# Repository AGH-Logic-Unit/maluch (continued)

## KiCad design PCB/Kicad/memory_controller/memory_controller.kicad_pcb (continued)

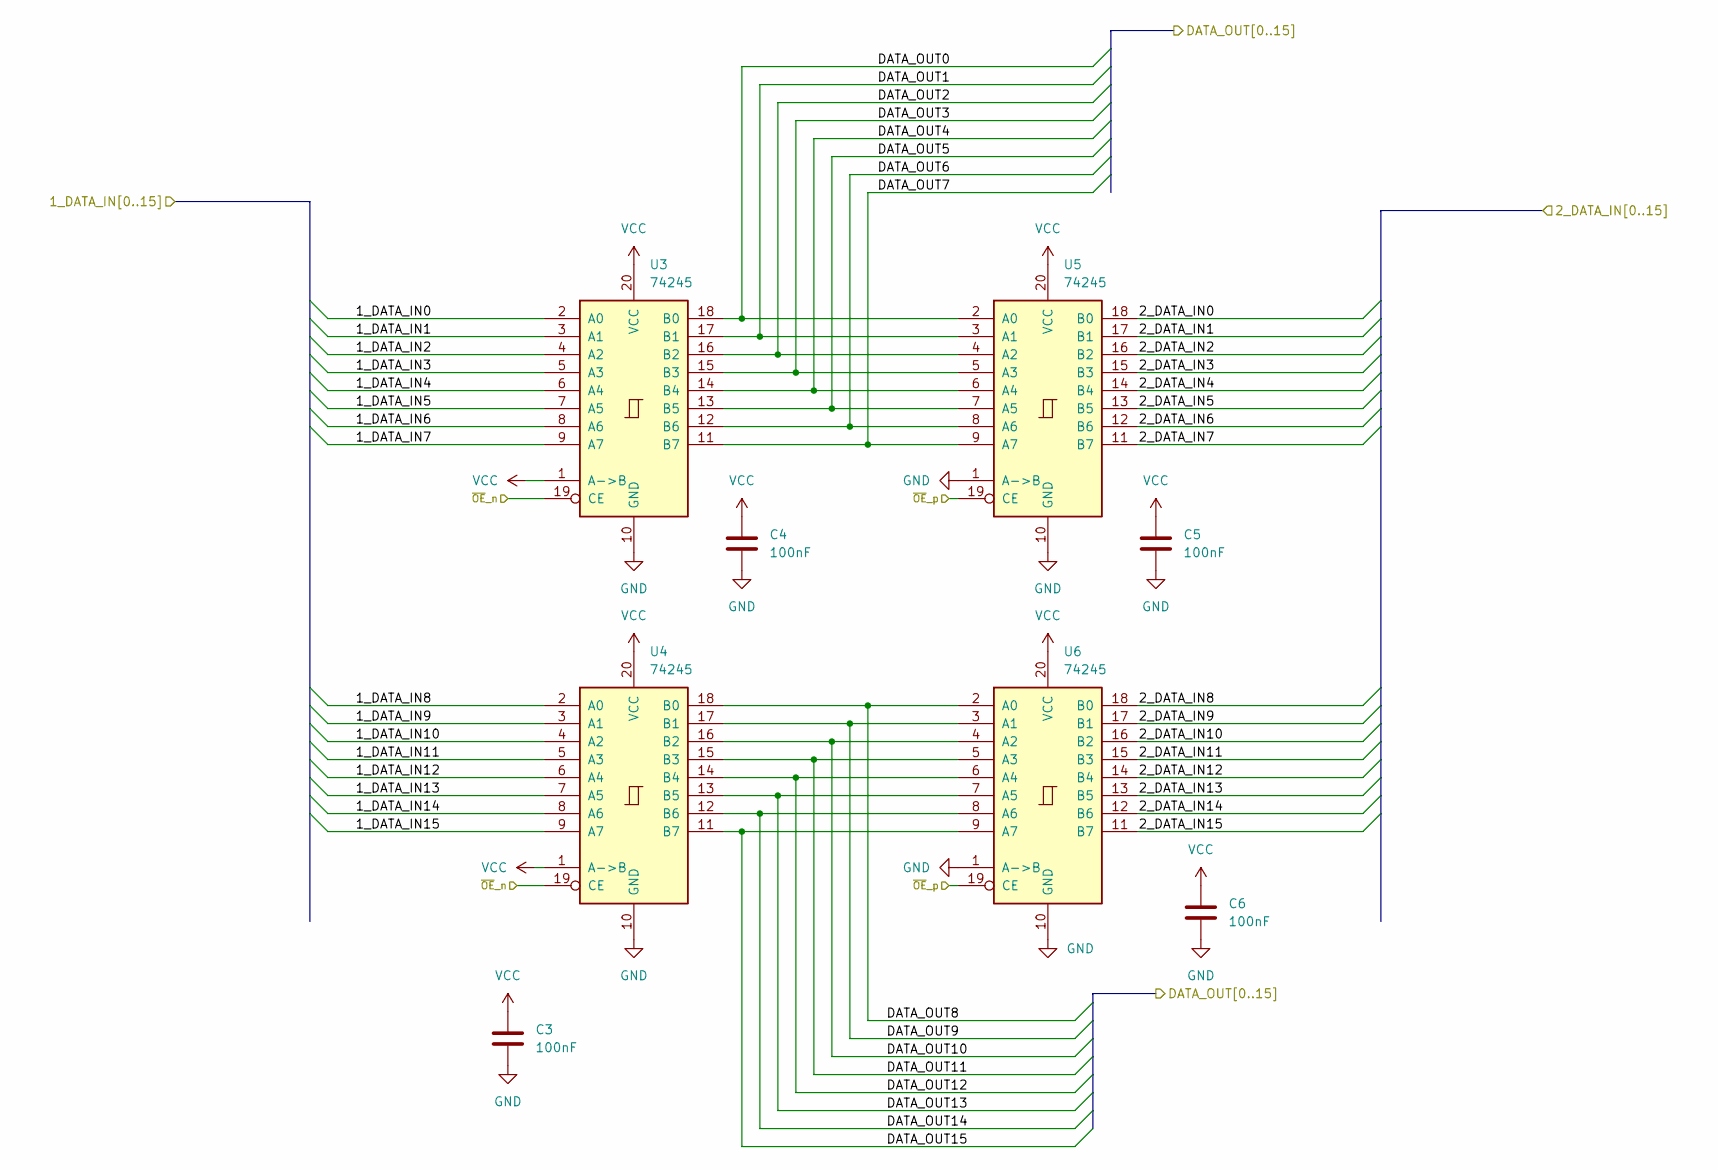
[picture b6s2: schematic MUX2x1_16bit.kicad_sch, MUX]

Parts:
C3, C4, C5, C6: 100nF; C_0402_1005Metric
U3, U4, U5, U6: 74245; TSSOP-20_4.4x6.5mm_P0.65mm

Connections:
/ADDER/DATA_OUT0: U5.18 (B0); also elsewhere on the board
/ADDER/DATA_OUT1: U5.17 (B1); also elsewhere on the board
/ADDER/DATA_OUT2: U5.16 (B2); also elsewhere on the board
/ADDER/DATA_OUT3: U5.15 (B3); also elsewhere on the board
/ADDER/DATA_OUT4: U5.14 (B4); also elsewhere on the board
/ADDER/DATA_OUT5: U5.13 (B5); also elsewhere on the board
/ADDER/DATA_OUT6: U5.12 (B6); also elsewhere on the board
/ADDER/DATA_OUT7: U5.11 (B7); also elsewhere on the board
/ADDER/DATA_OUT8: U6.18 (B0); also elsewhere on the board
/ADDER/DATA_OUT9: U6.17 (B1); also elsewhere on the board
/ADDER/DATA_OUT10: U6.16 (B2); also elsewhere on the board
/ADDER/DATA_OUT11: U6.15 (B3); also elsewhere on the board
/ADDER/DATA_OUT12: U6.14 (B4); also elsewhere on the board
/ADDER/DATA_OUT13: U6.13 (B5); also elsewhere on the board
/ADDER/DATA_OUT14: U6.12 (B6); also elsewhere on the board
/ADDER/DATA_OUT15: U6.11 (B7); also elsewhere on the board
/GPU_DATA0: U3.2 (A0); also elsewhere on the board
/GPU_DATA1: U3.3 (A1); also elsewhere on the board
/GPU_DATA2: U3.4 (A2); also elsewhere on the board
/GPU_DATA3: U3.5 (A3); also elsewhere on the board
/GPU_DATA4: U3.6 (A4); also elsewhere on the board
/GPU_DATA5: U3.7 (A5); also elsewhere on the board
/GPU_DATA6: U3.8 (A6); also elsewhere on the board
/GPU_DATA7: U3.9 (A7); also elsewhere on the board
/GPU_DATA8: U4.2 (A0); also elsewhere on the board
/GPU_DATA9: U4.3 (A1); also elsewhere on the board
/GPU_DATA10: U4.4 (A2); also elsewhere on the board
/GPU_DATA11: U4.5 (A3); also elsewhere on the board
/GPU_DATA12: U4.6 (A4); also elsewhere on the board
/GPU_DATA13: U4.7 (A5); also elsewhere on the board
/GPU_DATA14: U4.8 (A6); also elsewhere on the board
/GPU_DATA15: U4.9 (A7); also elsewhere on the board
/RegAddr/DATA_IN0: U3.18 (B0), U5.2 (A0); also elsewhere on the board
/RegAddr/DATA_IN1: U3.17 (B1), U5.3 (A1); also elsewhere on the board
/RegAddr/DATA_IN2: U3.16 (B2), U5.4 (A2); also elsewhere on the board
/RegAddr/DATA_IN3: U3.15 (B3), U5.5 (A3); also elsewhere on the board
/RegAddr/DATA_IN4: U3.14 (B4), U5.6 (A4); also elsewhere on the board
/RegAddr/DATA_IN5: U3.13 (B5), U5.7 (A5); also elsewhere on the board
/RegAddr/DATA_IN6: U3.12 (B6), U5.8 (A6); also elsewhere on the board
/RegAddr/DATA_IN7: U3.11 (B7), U5.9 (A7); also elsewhere on the board
/RegAddr/DATA_IN8: U4.18 (B0), U6.2 (A0); also elsewhere on the board
/RegAddr/DATA_IN9: U4.17 (B1), U6.3 (A1); also elsewhere on the board
/RegAddr/DATA_IN10: U4.16 (B2), U6.4 (A2); also elsewhere on the board
/RegAddr/DATA_IN11: U4.15 (B3), U6.5 (A3); also elsewhere on the board
/RegAddr/DATA_IN12: U4.14 (B4), U6.6 (A4); also elsewhere on the board
/RegAddr/DATA_IN13: U4.13 (B5), U6.7 (A5); also elsewhere on the board
/RegAddr/DATA_IN14: U4.12 (B6), U6.8 (A6); also elsewhere on the board
/RegAddr/DATA_IN15: U4.11 (B7), U6.9 (A7); also elsewhere on the board
/~OE_n: U3.19 (CE), U4.19 (CE); also elsewhere on the board
/~OE_p: U5.19 (CE), U6.19 (CE); also elsewhere on the board
GND: C3.1, C4.1, C5.1, C6.1, U3.10 (GND), U4.10 (GND), U5.1 (A->B), U5.10 (GND), U6.1 (A->B), U6.10 (GND); also elsewhere on the board
VCC: C3.2, C4.2, C5.2, C6.2, U3.1 (A->B), U3.20 (VCC), U4.1 (A->B), U4.20 (VCC), U5.20 (VCC), U6.20 (VCC); also elsewhere on the board

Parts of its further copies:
C15, C16, C17, C18: 100nF; C_0402_1005Metric
U15, U16, U17, U18: 74245; TSSOP-20_4.4x6.5mm_P0.65mm

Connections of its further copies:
/2xROM_AT28C256/IO0: U15.2 (A0); also elsewhere on the board
/2xROM_AT28C256/IO1: U15.3 (A1); also elsewhere on the board
/2xROM_AT28C256/IO2: U15.4 (A2); also elsewhere on the board
/2xROM_AT28C256/IO3: U15.5 (A3); also elsewhere on the board
/2xROM_AT28C256/IO4: U15.6 (A4); also elsewhere on the board
/2xROM_AT28C256/IO5: U15.7 (A5); also elsewhere on the board
/2xROM_AT28C256/IO6: U15.8 (A6); also elsewhere on the board
/2xROM_AT28C256/IO7: U15.9 (A7); also elsewhere on the board
/2xROM_AT28C256/IO8: U16.2 (A0); also elsewhere on the board
/2xROM_AT28C256/IO9: U16.3 (A1); also elsewhere on the board
/2xROM_AT28C256/IO10: U16.4 (A2); also elsewhere on the board
/2xROM_AT28C256/IO11: U16.5 (A3); also elsewhere on the board
/2xROM_AT28C256/IO12: U16.6 (A4); also elsewhere on the board
/2xROM_AT28C256/IO13: U16.7 (A5); also elsewhere on the board
/2xROM_AT28C256/IO14: U16.8 (A6); also elsewhere on the board
/2xROM_AT28C256/IO15: U16.9 (A7); also elsewhere on the board
/GPU_ADDR15: U15.19 (CE), U16.19 (CE); also elsewhere on the board
/GPU_DATA0: U17.18 (B0); also elsewhere on the board
/GPU_DATA1: U17.17 (B1); also elsewhere on the board
/GPU_DATA2: U17.16 (B2); also elsewhere on the board
/GPU_DATA3: U17.15 (B3); also elsewhere on the board
/GPU_DATA4: U17.14 (B4); also elsewhere on the board
/GPU_DATA5: U17.13 (B5); also elsewhere on the board
/GPU_DATA6: U17.12 (B6); also elsewhere on the board
/GPU_DATA7: U17.11 (B7); also elsewhere on the board
/GPU_DATA8: U18.18 (B0); also elsewhere on the board
/GPU_DATA9: U18.17 (B1); also elsewhere on the board
/GPU_DATA10: U18.16 (B2); also elsewhere on the board
/GPU_DATA11: U18.15 (B3); also elsewhere on the board
/GPU_DATA12: U18.14 (B4); also elsewhere on the board
/GPU_DATA13: U18.13 (B5); also elsewhere on the board
/GPU_DATA14: U18.12 (B6); also elsewhere on the board
/GPU_DATA15: U18.11 (B7); also elsewhere on the board
/output_MUX/DATA_OUT0: U15.18 (B0), U17.2 (A0); also elsewhere on the board
/output_MUX/DATA_OUT1: U15.17 (B1), U17.3 (A1); also elsewhere on the board
/output_MUX/DATA_OUT2: U15.16 (B2), U17.4 (A2); also elsewhere on the board
/output_MUX/DATA_OUT3: U15.15 (B3), U17.5 (A3); also elsewhere on the board
/output_MUX/DATA_OUT4: U15.14 (B4), U17.6 (A4); also elsewhere on the board
/output_MUX/DATA_OUT5: U15.13 (B5), U17.7 (A5); also elsewhere on the board
/output_MUX/DATA_OUT6: U15.12 (B6), U17.8 (A6); also elsewhere on the board
/output_MUX/DATA_OUT7: U15.11 (B7), U17.9 (A7); also elsewhere on the board
/output_MUX/DATA_OUT8: U16.18 (B0), U18.2 (A0); also elsewhere on the board
/output_MUX/DATA_OUT9: U16.17 (B1), U18.3 (A1); also elsewhere on the board
/output_MUX/DATA_OUT10: U16.16 (B2), U18.4 (A2); also elsewhere on the board
/output_MUX/DATA_OUT11: U16.15 (B3), U18.5 (A3); also elsewhere on the board
/output_MUX/DATA_OUT12: U16.14 (B4), U18.6 (A4); also elsewhere on the board
/output_MUX/DATA_OUT13: U16.13 (B5), U18.7 (A5); also elsewhere on the board
/output_MUX/DATA_OUT14: U16.12 (B6), U18.8 (A6); also elsewhere on the board
/output_MUX/DATA_OUT15: U16.11 (B7), U18.9 (A7); also elsewhere on the board
/~OE_MUX_n: U17.19 (CE), U18.19 (CE); also elsewhere on the board
GND: C15.1, C16.1, C17.1, C18.1, U15.10 (GND), U16.10 (GND), U17.1 (A->B), U17.10 (GND), U18.1 (A->B), U18.10 (GND); also elsewhere on the board
VCC: C15.2, C16.2, C17.2, C18.2, U15.1 (A->B), U15.20 (VCC), U16.1 (A->B), U16.20 (VCC), U17.20 (VCC), U18.20 (VCC); also elsewhere on the board

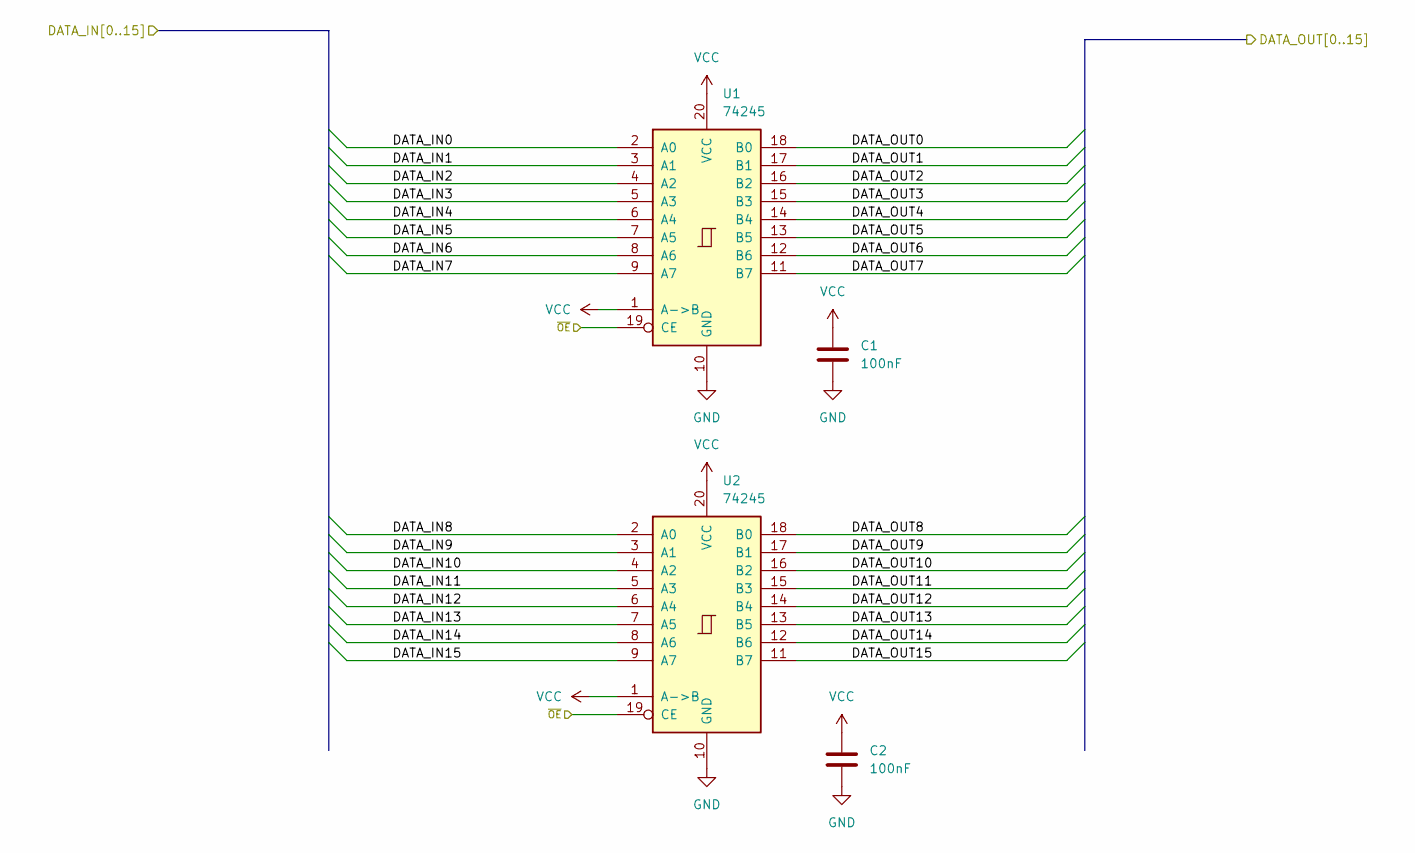
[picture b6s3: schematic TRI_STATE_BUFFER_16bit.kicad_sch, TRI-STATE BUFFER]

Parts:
C1, C2: 100nF; C_0402_1005Metric
U1, U2: 74245; TSSOP-20_4.4x6.5mm_P0.65mm

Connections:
/DATA_BUS0: U1.2 (A0); also elsewhere on the board
/DATA_BUS1: U1.3 (A1); also elsewhere on the board
/DATA_BUS2: U1.4 (A2); also elsewhere on the board
/DATA_BUS3: U1.5 (A3); also elsewhere on the board
/DATA_BUS4: U1.6 (A4); also elsewhere on the board
/DATA_BUS5: U1.7 (A5); also elsewhere on the board
/DATA_BUS6: U1.8 (A6); also elsewhere on the board
/DATA_BUS7: U1.9 (A7); also elsewhere on the board
/DATA_BUS8: U2.2 (A0); also elsewhere on the board
/DATA_BUS9: U2.3 (A1); also elsewhere on the board
/DATA_BUS10: U2.4 (A2); also elsewhere on the board
/DATA_BUS11: U2.5 (A3); also elsewhere on the board
/DATA_BUS12: U2.6 (A4); also elsewhere on the board
/DATA_BUS13: U2.7 (A5); also elsewhere on the board
/DATA_BUS14: U2.8 (A6); also elsewhere on the board
/DATA_BUS15: U2.9 (A7); also elsewhere on the board
/GPU_DATA0: U1.18 (B0); also elsewhere on the board
/GPU_DATA1: U1.17 (B1); also elsewhere on the board
/GPU_DATA2: U1.16 (B2); also elsewhere on the board
/GPU_DATA3: U1.15 (B3); also elsewhere on the board
/GPU_DATA4: U1.14 (B4); also elsewhere on the board
/GPU_DATA5: U1.13 (B5); also elsewhere on the board
/GPU_DATA6: U1.12 (B6); also elsewhere on the board
/GPU_DATA7: U1.11 (B7); also elsewhere on the board
/GPU_DATA8: U2.18 (B0); also elsewhere on the board
/GPU_DATA9: U2.17 (B1); also elsewhere on the board
/GPU_DATA10: U2.16 (B2); also elsewhere on the board
/GPU_DATA11: U2.15 (B3); also elsewhere on the board
/GPU_DATA12: U2.14 (B4); also elsewhere on the board
/GPU_DATA13: U2.13 (B5); also elsewhere on the board
/GPU_DATA14: U2.12 (B6); also elsewhere on the board
/GPU_DATA15: U2.11 (B7); also elsewhere on the board
/OUTPUT_ENABLE: U1.19 (CE), U2.19 (CE); also elsewhere on the board
GND: C1.1, C2.1, U1.10 (GND), U2.10 (GND); also elsewhere on the board
VCC: C1.2, C2.2, U1.1 (A->B), U1.20 (VCC), U2.1 (A->B), U2.20 (VCC); also elsewhere on the board

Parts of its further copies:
C13, C14: 100nF; C_0402_1005Metric
U13, U14: 74245; TSSOP-20_4.4x6.5mm_P0.65mm

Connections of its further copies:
/DATA_BUS0: U13.18 (B0); also elsewhere on the board
/DATA_BUS1: U13.17 (B1); also elsewhere on the board
/DATA_BUS2: U13.16 (B2); also elsewhere on the board
/DATA_BUS3: U13.15 (B3); also elsewhere on the board
/DATA_BUS4: U13.14 (B4); also elsewhere on the board
/DATA_BUS5: U13.13 (B5); also elsewhere on the board
/DATA_BUS6: U13.12 (B6); also elsewhere on the board
/DATA_BUS7: U13.11 (B7); also elsewhere on the board
/DATA_BUS8: U14.18 (B0); also elsewhere on the board
/DATA_BUS9: U14.17 (B1); also elsewhere on the board
/DATA_BUS10: U14.16 (B2); also elsewhere on the board
/DATA_BUS11: U14.15 (B3); also elsewhere on the board
/DATA_BUS12: U14.14 (B4); also elsewhere on the board
/DATA_BUS13: U14.13 (B5); also elsewhere on the board
/DATA_BUS14: U14.12 (B6); also elsewhere on the board
/DATA_BUS15: U14.11 (B7); also elsewhere on the board
/output_MUX/DATA_OUT0: U13.2 (A0); also elsewhere on the board
/output_MUX/DATA_OUT1: U13.3 (A1); also elsewhere on the board
/output_MUX/DATA_OUT2: U13.4 (A2); also elsewhere on the board
/output_MUX/DATA_OUT3: U13.5 (A3); also elsewhere on the board
/output_MUX/DATA_OUT4: U13.6 (A4); also elsewhere on the board
/output_MUX/DATA_OUT5: U13.7 (A5); also elsewhere on the board
/output_MUX/DATA_OUT6: U13.8 (A6); also elsewhere on the board
/output_MUX/DATA_OUT7: U13.9 (A7); also elsewhere on the board
/output_MUX/DATA_OUT8: U14.2 (A0); also elsewhere on the board
/output_MUX/DATA_OUT9: U14.3 (A1); also elsewhere on the board
/output_MUX/DATA_OUT10: U14.4 (A2); also elsewhere on the board
/output_MUX/DATA_OUT11: U14.5 (A3); also elsewhere on the board
/output_MUX/DATA_OUT12: U14.6 (A4); also elsewhere on the board
/output_MUX/DATA_OUT13: U14.7 (A5); also elsewhere on the board
/output_MUX/DATA_OUT14: U14.8 (A6); also elsewhere on the board
/output_MUX/DATA_OUT15: U14.9 (A7); also elsewhere on the board
/~OUTPUT_ENABLE: U13.19 (CE), U14.19 (CE); also elsewhere on the board
GND: C13.1, C14.1, U13.10 (GND), U14.10 (GND); also elsewhere on the board
VCC: C13.2, C14.2, U13.1 (A->B), U13.20 (VCC), U14.1 (A->B), U14.20 (VCC); also elsewhere on the board

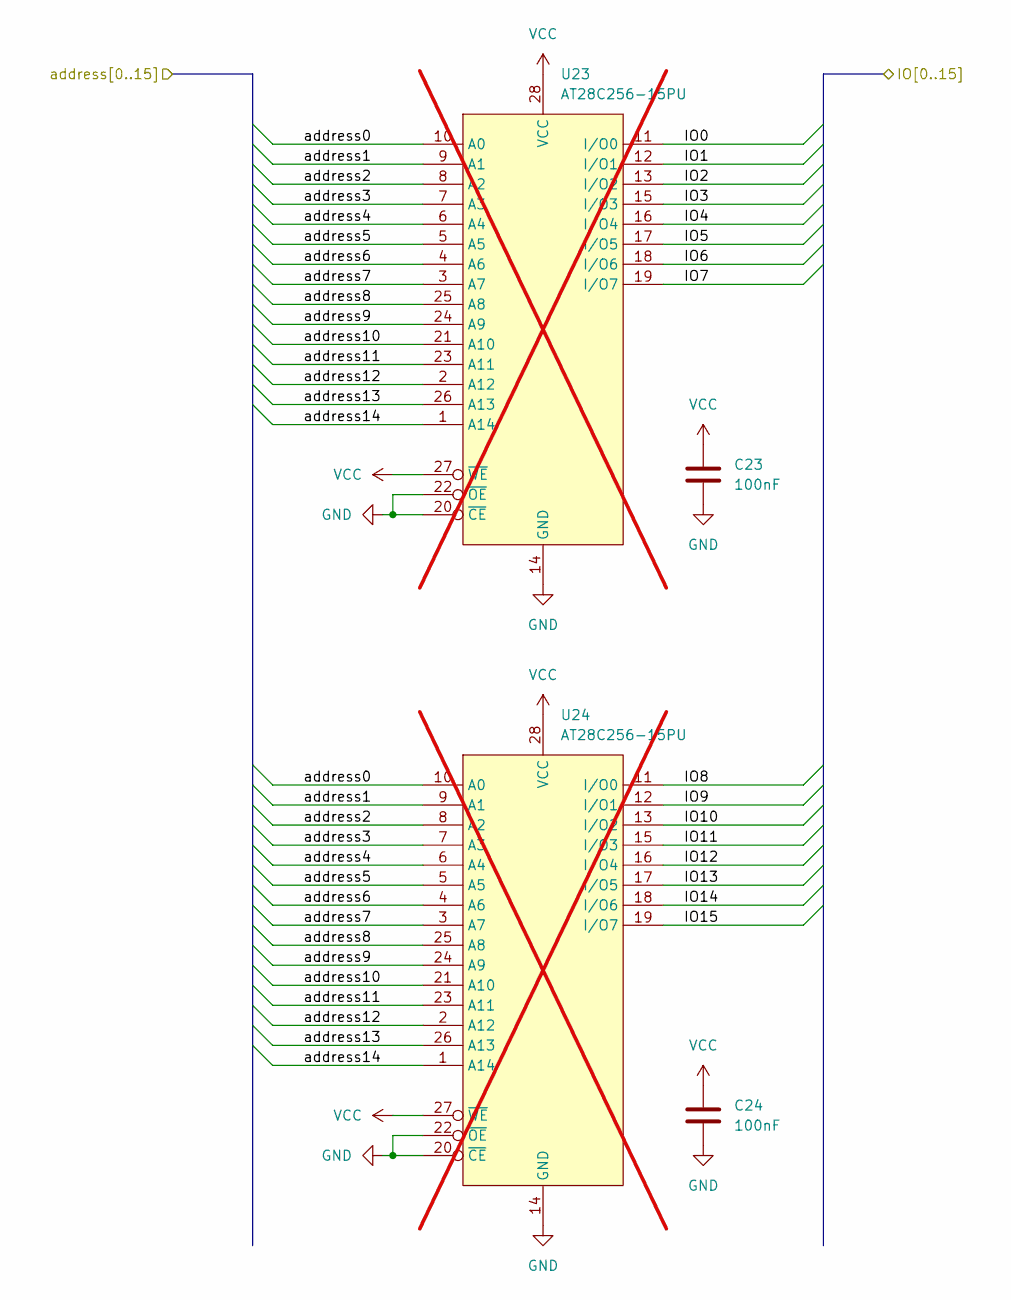
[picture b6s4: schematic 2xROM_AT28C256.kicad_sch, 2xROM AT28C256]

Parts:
C23, C24: 100nF; C_0402_1005Metric
U23, U24: AT28C256-15PU; DIP-28_W15.24mm_Socket; not fitted

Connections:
/2xROM_AT28C256/IO0: U23.11 (I/O0); also elsewhere on the board
/2xROM_AT28C256/IO1: U23.12 (I/O1); also elsewhere on the board
/2xROM_AT28C256/IO2: U23.13 (I/O2); also elsewhere on the board
/2xROM_AT28C256/IO3: U23.15 (I/O3); also elsewhere on the board
/2xROM_AT28C256/IO4: U23.16 (I/O4); also elsewhere on the board
/2xROM_AT28C256/IO5: U23.17 (I/O5); also elsewhere on the board
/2xROM_AT28C256/IO6: U23.18 (I/O6); also elsewhere on the board
/2xROM_AT28C256/IO7: U23.19 (I/O7); also elsewhere on the board
/2xROM_AT28C256/IO8: U24.11 (I/O0); also elsewhere on the board
/2xROM_AT28C256/IO9: U24.12 (I/O1); also elsewhere on the board
/2xROM_AT28C256/IO10: U24.13 (I/O2); also elsewhere on the board
/2xROM_AT28C256/IO11: U24.15 (I/O3); also elsewhere on the board
/2xROM_AT28C256/IO12: U24.16 (I/O4); also elsewhere on the board
/2xROM_AT28C256/IO13: U24.17 (I/O5); also elsewhere on the board
/2xROM_AT28C256/IO14: U24.18 (I/O6); also elsewhere on the board
/2xROM_AT28C256/IO15: U24.19 (I/O7); also elsewhere on the board
/GPU_ADDR0: U23.10 (A0), U24.10 (A0); also elsewhere on the board
/GPU_ADDR1: U23.9 (A1), U24.9 (A1); also elsewhere on the board
/GPU_ADDR2: U23.8 (A2), U24.8 (A2); also elsewhere on the board
/GPU_ADDR3: U23.7 (A3), U24.7 (A3); also elsewhere on the board
/GPU_ADDR4: U23.6 (A4), U24.6 (A4); also elsewhere on the board
/GPU_ADDR5: U23.5 (A5), U24.5 (A5); also elsewhere on the board
/GPU_ADDR6: U23.4 (A6), U24.4 (A6); also elsewhere on the board
/GPU_ADDR7: U23.3 (A7), U24.3 (A7); also elsewhere on the board
/GPU_ADDR8: U23.25 (A8), U24.25 (A8); also elsewhere on the board
/GPU_ADDR9: U23.24 (A9), U24.24 (A9); also elsewhere on the board
/GPU_ADDR10: U23.21 (A10), U24.21 (A10); also elsewhere on the board
/GPU_ADDR11: U23.23 (A11), U24.23 (A11); also elsewhere on the board
/GPU_ADDR12: U23.2 (A12), U24.2 (A12); also elsewhere on the board
/GPU_ADDR13: U23.26 (A13), U24.26 (A13); also elsewhere on the board
/GPU_ADDR14: U23.1 (A14), U24.1 (A14); also elsewhere on the board
GND: C23.1, C24.1, U23.14 (GND), U23.20 (~CE), U23.22 (~OE), U24.14 (GND), U24.20 (~CE), U24.22 (~OE); also elsewhere on the board
VCC: C23.2, C24.2, U23.27 (~WE), U23.28 (VCC), U24.27 (~WE), U24.28 (VCC); also elsewhere on the board

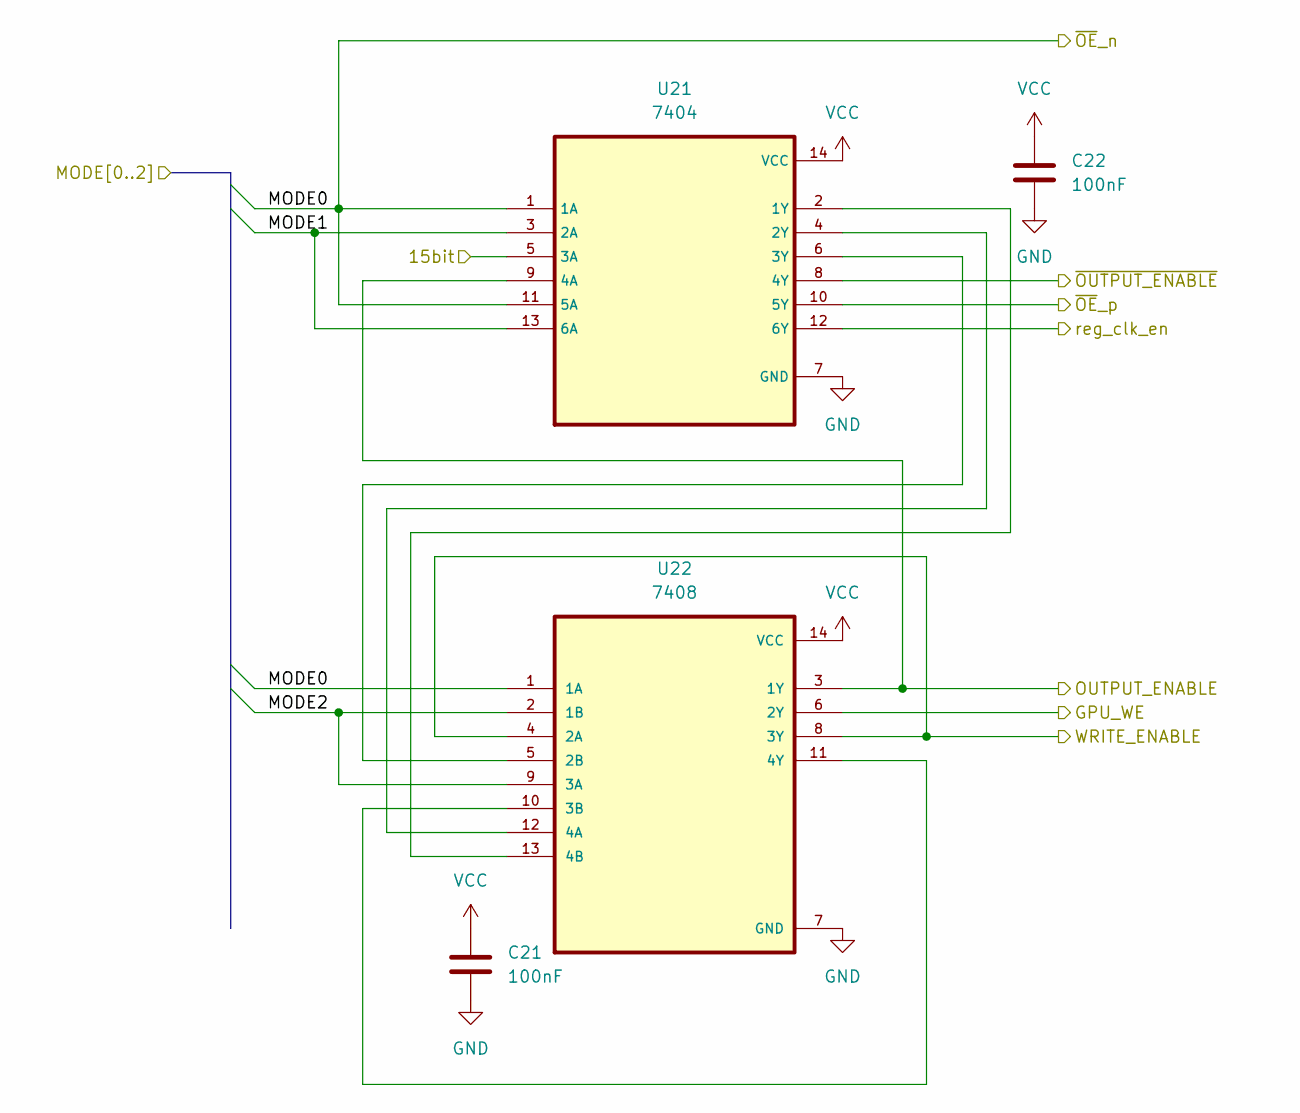
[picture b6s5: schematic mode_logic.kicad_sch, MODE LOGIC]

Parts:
C21, C22: 100nF; C_0402_1005Metric
U21: 7404; SO-14_3.9x8.65mm_P1.27mm
U22: 7408; SO-14_3.9x8.65mm_P1.27mm

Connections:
/GPU_ADDR15: U21.5 (3A); also elsewhere on the board
/GPU_WE: U22.6 (2Y); also elsewhere on the board
/MODE1: U21.3 (2A), U21.13 (6A); also elsewhere on the board
/MODE2: U22.2 (1B), U22.9 (3A); also elsewhere on the board
/OUTPUT_ENABLE: U21.9 (4A), U22.3 (1Y); also elsewhere on the board
/RegAddr/~CLK_en: U21.12 (6Y); also elsewhere on the board
/WRITE_ENABLE: U22.4 (2A), U22.8 (3Y); also elsewhere on the board
/~OE_n: U21.1 (1A), U21.11 (5A), U22.1 (1A); also elsewhere on the board
/~OE_p: U21.10 (5Y); also elsewhere on the board
/~OUTPUT_ENABLE: U21.8 (4Y); also elsewhere on the board
GND: C21.1, C22.1, U21.7 (GND), U22.7 (GND); also elsewhere on the board
unnamed: U21.2 (1Y), U22.13 (4B)
unnamed: U21.4 (2Y), U22.12 (4A)
unnamed: U21.6 (3Y), U22.5 (2B)
unnamed: U22.10 (3B), U22.11 (4Y)
VCC: C21.2, C22.2, U21.14 (VCC), U22.14 (VCC); also elsewhere on the board

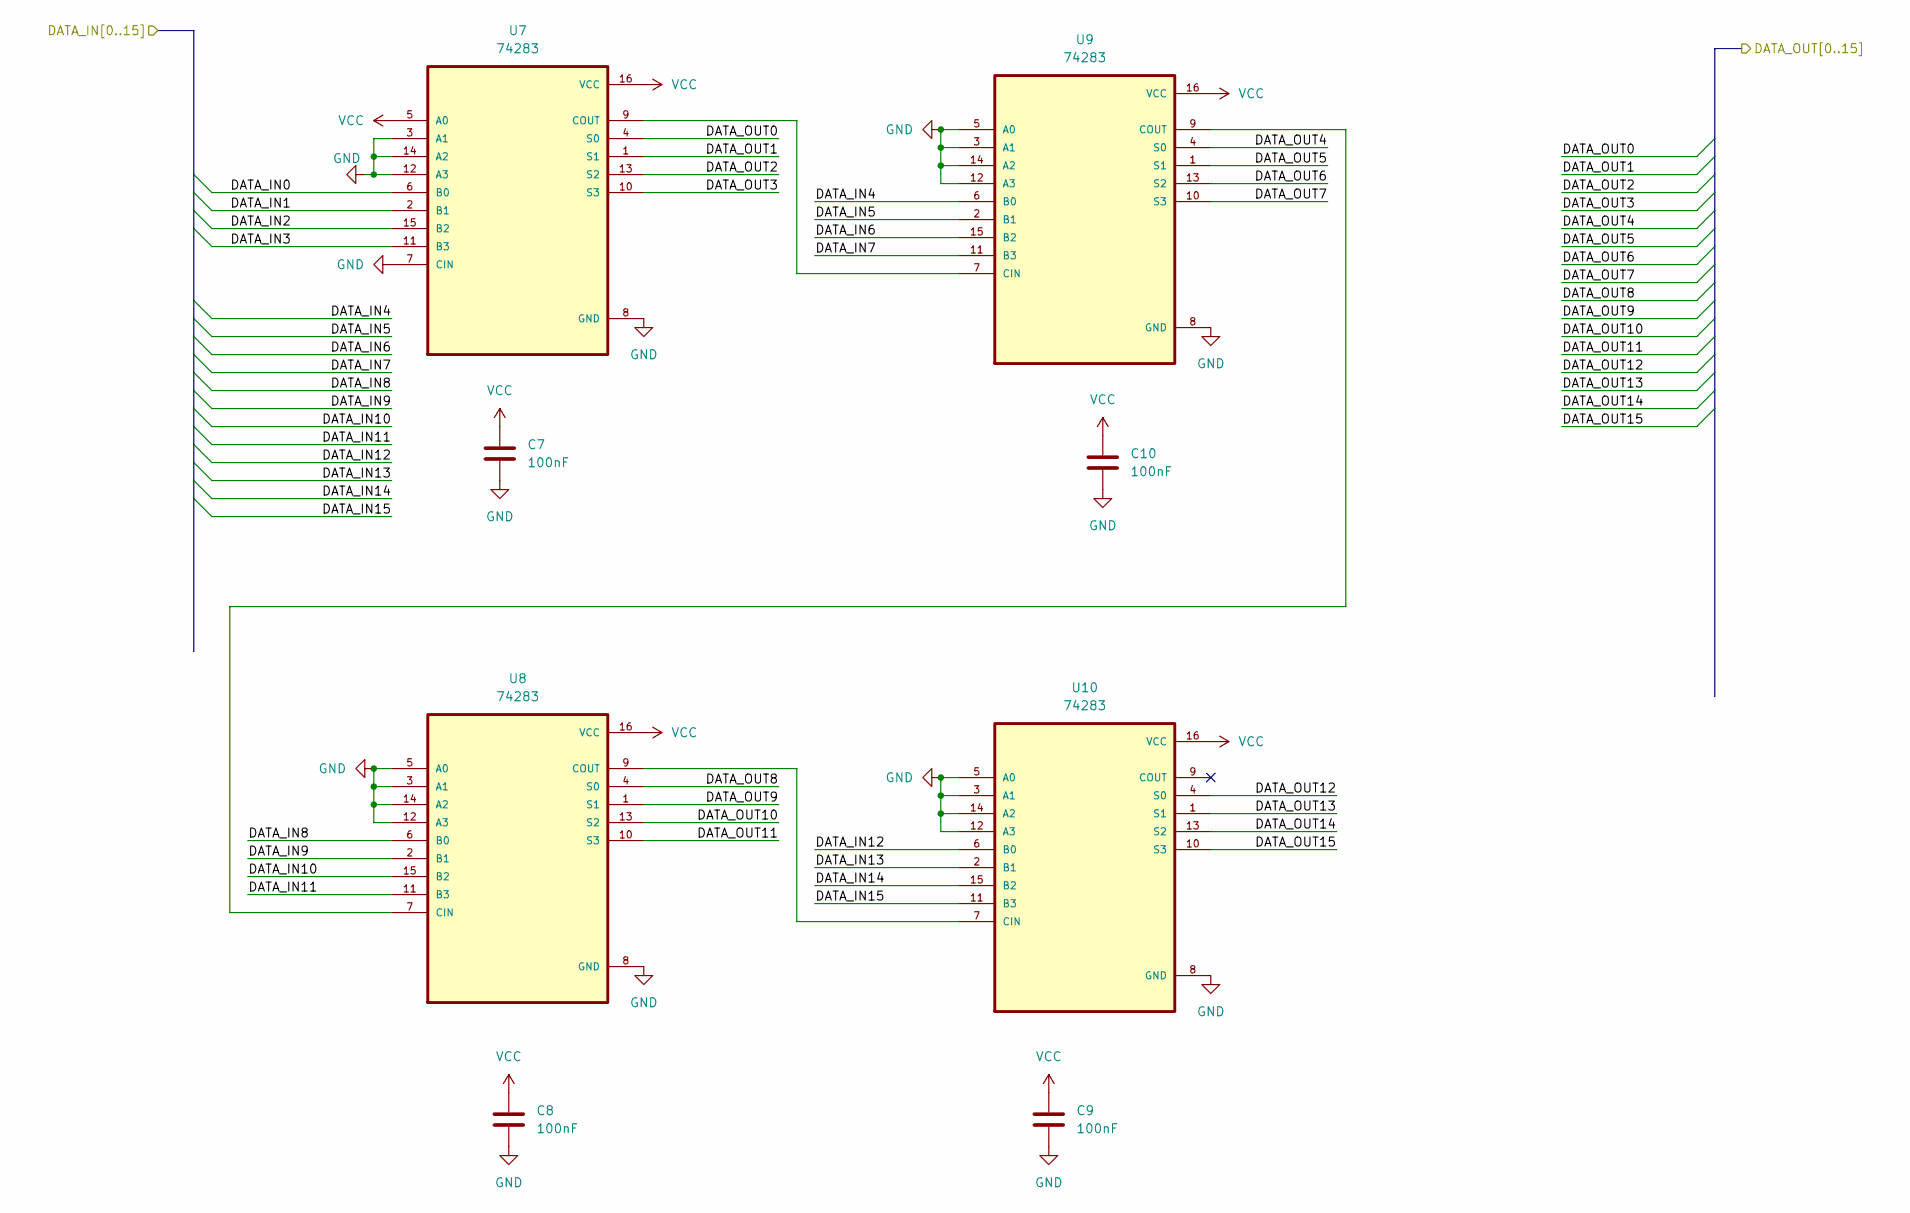
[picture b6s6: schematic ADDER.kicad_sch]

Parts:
C7, C8, C9, C10: 100nF; C_0402_1005Metric
U7, U8, U9, U10: 74283; SOIC-16_3.9x9.9mm_P1.27mm

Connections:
/ADDER/DATA_OUT0: U7.4 (S0); also elsewhere on the board
/ADDER/DATA_OUT1: U7.1 (S1); also elsewhere on the board
/ADDER/DATA_OUT2: U7.13 (S2); also elsewhere on the board
/ADDER/DATA_OUT3: U7.10 (S3); also elsewhere on the board
/ADDER/DATA_OUT4: U9.4 (S0); also elsewhere on the board
/ADDER/DATA_OUT5: U9.1 (S1); also elsewhere on the board
/ADDER/DATA_OUT6: U9.13 (S2); also elsewhere on the board
/ADDER/DATA_OUT7: U9.10 (S3); also elsewhere on the board
/ADDER/DATA_OUT8: U8.4 (S0); also elsewhere on the board
/ADDER/DATA_OUT9: U8.1 (S1); also elsewhere on the board
/ADDER/DATA_OUT10: U8.13 (S2); also elsewhere on the board
/ADDER/DATA_OUT11: U8.10 (S3); also elsewhere on the board
/ADDER/DATA_OUT12: U10.4 (S0); also elsewhere on the board
/ADDER/DATA_OUT13: U10.1 (S1); also elsewhere on the board
/ADDER/DATA_OUT14: U10.13 (S2); also elsewhere on the board
/ADDER/DATA_OUT15: U10.10 (S3); also elsewhere on the board
/GPU_ADDR0: U7.6 (B0); also elsewhere on the board
/GPU_ADDR1: U7.2 (B1); also elsewhere on the board
/GPU_ADDR2: U7.15 (B2); also elsewhere on the board
/GPU_ADDR3: U7.11 (B3); also elsewhere on the board
/GPU_ADDR4: U9.6 (B0); also elsewhere on the board
/GPU_ADDR5: U9.2 (B1); also elsewhere on the board
/GPU_ADDR6: U9.15 (B2); also elsewhere on the board
/GPU_ADDR7: U9.11 (B3); also elsewhere on the board
/GPU_ADDR8: U8.6 (B0); also elsewhere on the board
/GPU_ADDR9: U8.2 (B1); also elsewhere on the board
/GPU_ADDR10: U8.15 (B2); also elsewhere on the board
/GPU_ADDR11: U8.11 (B3); also elsewhere on the board
/GPU_ADDR12: U10.6 (B0); also elsewhere on the board
/GPU_ADDR13: U10.2 (B1); also elsewhere on the board
/GPU_ADDR14: U10.15 (B2); also elsewhere on the board
/GPU_ADDR15: U10.11 (B3); also elsewhere on the board
GND: C7.1, C8.1, C9.1, C10.1, U7.3 (A1), U7.7 (CIN), U7.8 (GND), U7.12 (A3), U7.14 (A2), U8.3 (A1), U8.5 (A0), U8.8 (GND), U8.12 (A3), U8.14 (A2), U9.3 (A1), U9.5 (A0), U9.8 (GND), U9.12 (A3), U9.14 (A2), U10.3 (A1), U10.5 (A0), U10.8 (GND), U10.12 (A3), U10.14 (A2); also elsewhere on the board
unnamed: U7.9 (COUT), U9.7 (CIN)
unnamed: U8.7 (CIN), U9.9 (COUT)
unnamed: U8.9 (COUT), U10.7 (CIN)
VCC: C7.2, C8.2, C9.2, C10.2, U7.5 (A0), U7.16 (VCC), U8.16 (VCC), U9.16 (VCC), U10.16 (VCC); also elsewhere on the board

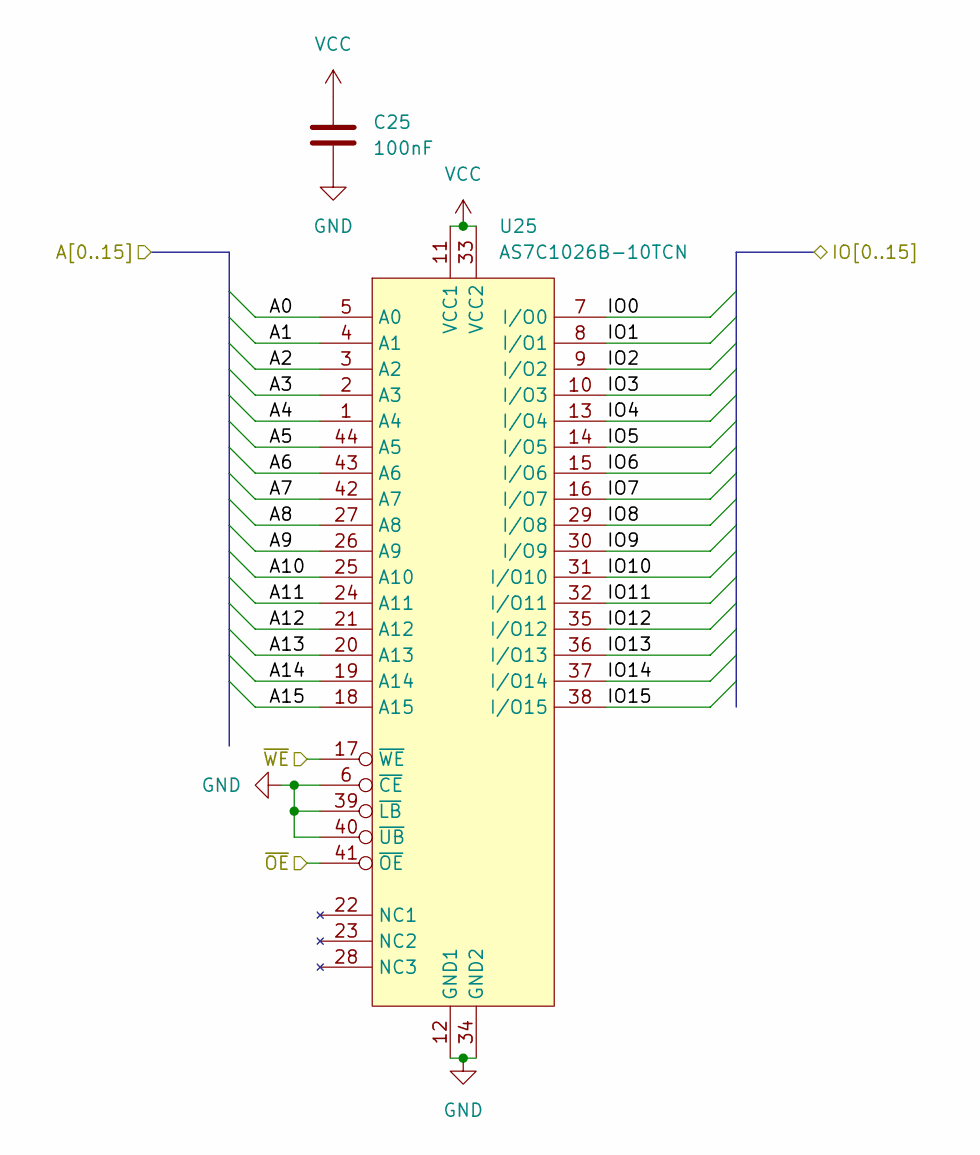
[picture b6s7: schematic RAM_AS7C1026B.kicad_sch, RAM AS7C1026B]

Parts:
C25: 100nF; C_0402_1005Metric
U25: AS7C1026B-10TCN; TSOP-II-44_10.16x18.41mm_P0.8mm

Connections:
/GPU_ADDR0: U25.5 (A0); also elsewhere on the board
/GPU_ADDR1: U25.4 (A1); also elsewhere on the board
/GPU_ADDR2: U25.3 (A2); also elsewhere on the board
/GPU_ADDR3: U25.2 (A3); also elsewhere on the board
/GPU_ADDR4: U25.1 (A4); also elsewhere on the board
/GPU_ADDR5: U25.44 (A5); also elsewhere on the board
/GPU_ADDR6: U25.43 (A6); also elsewhere on the board
/GPU_ADDR7: U25.42 (A7); also elsewhere on the board
/GPU_ADDR8: U25.27 (A8); also elsewhere on the board
/GPU_ADDR9: U25.26 (A9); also elsewhere on the board
/GPU_ADDR10: U25.25 (A10); also elsewhere on the board
/GPU_ADDR11: U25.24 (A11); also elsewhere on the board
/GPU_ADDR12: U25.21 (A12); also elsewhere on the board
/GPU_ADDR13: U25.20 (A13); also elsewhere on the board
/GPU_ADDR14: U25.19 (A14); also elsewhere on the board
/GPU_ADDR15: U25.18 (A15); also elsewhere on the board
/GPU_DATA0: U25.7 (I/O0); also elsewhere on the board
/GPU_DATA1: U25.8 (I/O1); also elsewhere on the board
/GPU_DATA2: U25.9 (I/O2); also elsewhere on the board
/GPU_DATA3: U25.10 (I/O3); also elsewhere on the board
/GPU_DATA4: U25.13 (I/O4); also elsewhere on the board
/GPU_DATA5: U25.14 (I/O5); also elsewhere on the board
/GPU_DATA6: U25.15 (I/O6); also elsewhere on the board
/GPU_DATA7: U25.16 (I/O7); also elsewhere on the board
/GPU_DATA8: U25.29 (I/O8); also elsewhere on the board
/GPU_DATA9: U25.30 (I/O9); also elsewhere on the board
/GPU_DATA10: U25.31 (I/O10); also elsewhere on the board
/GPU_DATA11: U25.32 (I/O11); also elsewhere on the board
/GPU_DATA12: U25.35 (I/O12); also elsewhere on the board
/GPU_DATA13: U25.36 (I/O13); also elsewhere on the board
/GPU_DATA14: U25.37 (I/O14); also elsewhere on the board
/GPU_DATA15: U25.38 (I/O15); also elsewhere on the board
/~OUTPUT_ENABLE: U25.41 (~OE); also elsewhere on the board
/~WE_mem: U25.17 (~WE); also elsewhere on the board
GND: C25.1, U25.6 (~CE), U25.12 (GND1), U25.34 (GND2), U25.39 (~LB), U25.40 (~UB); also elsewhere on the board
VCC: C25.2, U25.11 (VCC1), U25.33 (VCC2); also elsewhere on the board
